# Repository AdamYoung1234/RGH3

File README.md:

# RGH3 Adapter Board
Small RGH3 adapter board should work with Phat and Slim model.

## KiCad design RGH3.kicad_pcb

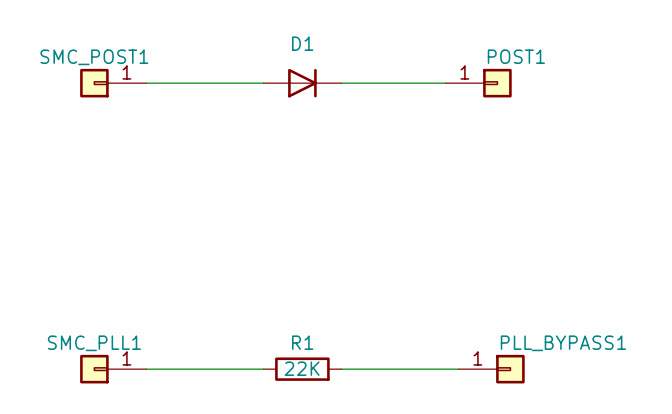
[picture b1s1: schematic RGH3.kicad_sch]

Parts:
D1: 1N4148W; D_SOD-123
PLL_BYPASS1: Conn_01x01; TestPoint_Pad_D1.5mm
POST1: Conn_01x01; TestPoint_Pad_D1.5mm
R1: 22K; R_0805_2012Metric
SMC_PLL1: Conn_01x01; TestPoint_Pad_D1.5mm
SMC_POST1: Conn_01x01; TestPoint_Pad_D1.5mm

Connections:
unnamed: D1.1 (K), POST1.1
unnamed: D1.2 (A), SMC_POST1.1
unnamed: PLL_BYPASS1.1, R1.2
unnamed: R1.1, SMC_PLL1.1

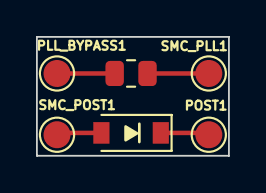
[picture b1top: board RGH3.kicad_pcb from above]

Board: 2 copper layers, 10.7 x 6.6 mm, 6 parts (0 on the bottom side), 4 nets.
